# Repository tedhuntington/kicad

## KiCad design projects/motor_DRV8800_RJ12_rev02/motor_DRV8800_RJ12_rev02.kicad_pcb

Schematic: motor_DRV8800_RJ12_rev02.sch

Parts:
C1, C3, C4: .1uF (50v)
H1, H2: HOLE
J1, J2: TERMINAL_2X1
R1, R2: 3.3k
R3, R4, R5: 1k
R6: 10m
U1: DRV8800_RTY
U2: RJ12

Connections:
CS: R6.1, U1.7 (SENSE), U2.2
GND: C4.2, J1.2, R6.2, U1.2 (GND), U1.12 (GND), U1.17 (PAD), U2.1
MODE: R3.2, U1.16 (MODE)
Motor1OutA: J2.1, U1.6 (OUT+)
Motor1OutB: J2.2, U1.9 (OUT-)
unnamed: C1.1, U1.11 (CP2)
unnamed: C1.2, U1.10 (CP1)
unnamed: C3.2, U1.13 (VCP)
unnamed: R2.2, U1.15 (nFAULT)
unnamed: R1.2, U1.3 (nSLEEP)
unnamed: R5.2, U2.5
unnamed: R4.1, U2.3
unnamed: R3.1, U2.4
PHASE: R5.1, U1.1 (PHASE)
PWM: R4.2, U1.4 (ENABLE)
VDD: R1.1, R2.1, U2.6
Vin: C3.1, C4.1, J1.1, U1.8 (VBB)

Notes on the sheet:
8 to 36v
Out to Motor
Motor power source
VDD=3.3V
(0.5w)
note: above resistors protect MCU against short from motor driver failure

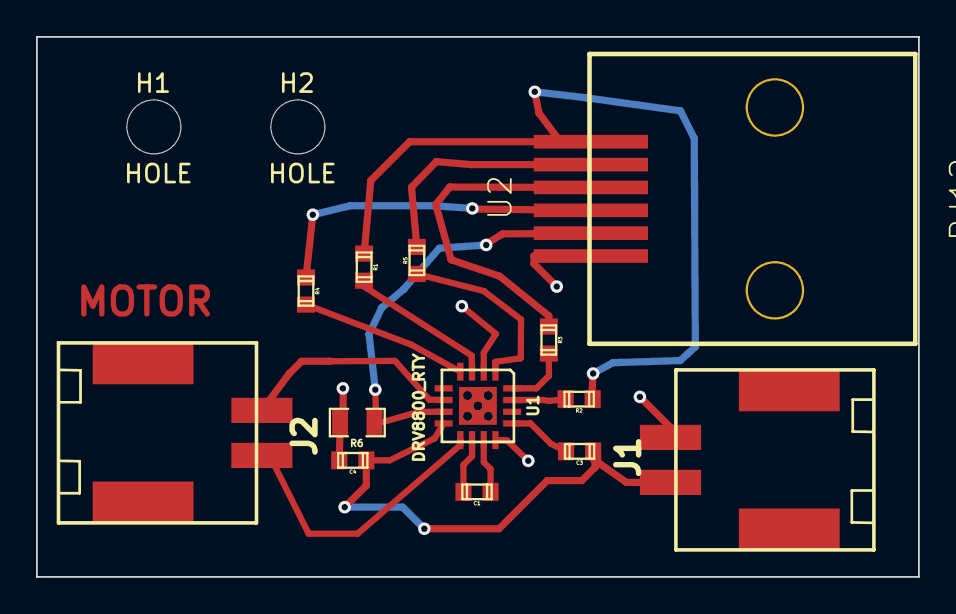
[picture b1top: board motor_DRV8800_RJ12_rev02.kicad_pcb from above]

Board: 2 copper layers, 49.0 x 30.0 mm, 15 parts (0 on the bottom side), 17 nets.

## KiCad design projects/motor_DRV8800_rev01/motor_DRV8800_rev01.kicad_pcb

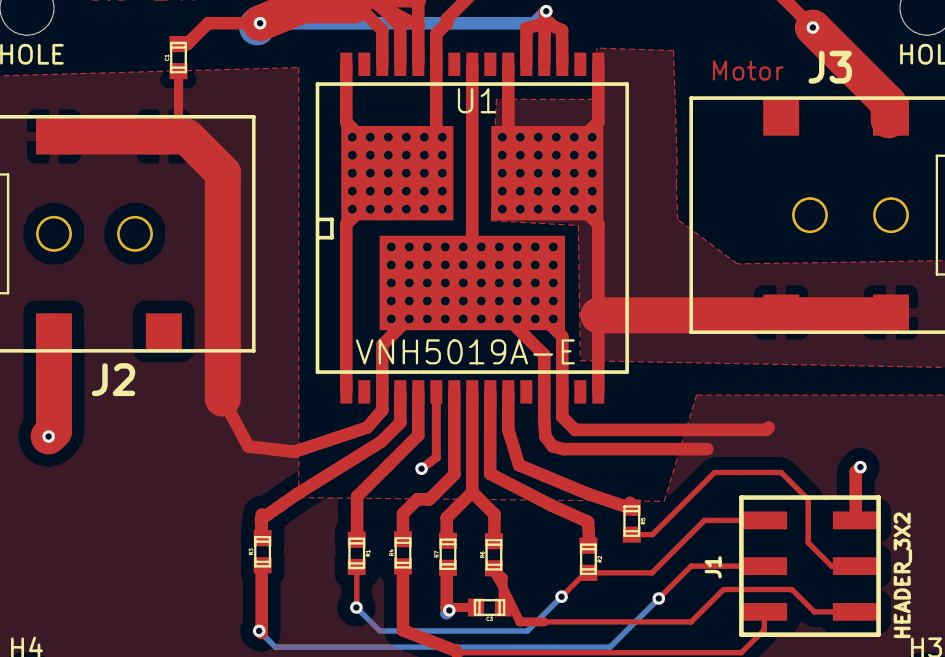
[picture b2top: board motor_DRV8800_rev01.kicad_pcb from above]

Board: 2 copper layers, 17 parts (0 on the bottom side), 15 nets.

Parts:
C1: .1uF (50v); TED_SM0603
C3: 33nF; TED_SM0603
H1, H2, H3, H4: HOLE; TED_Hole_3mm
J1: HEADER_3X2; TED_HEADER_3x2_SMT
J2, J3: DC_2.1MM; TED_DC_2.1mm_SMT
R1, R2: 3.3k; TED_SM0603
R3, R4, R5: 1k; TED_SM0603
R6: 10k; TED_SM0603
R7: 1.5k; TED_SM0603
U1: VNH5019A-E; TED_MultiPowerSO-30

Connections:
+2.8v: J1.1, R1.2, R2.2
CS: R6.2, R7.2, U1.8
GND: C1.2, C3.2, J1.6, J2.2, R7.1, U1.6, U1.18, U1.19, U1.20, U1.26, U1.27, U1.28
IN_A: R3.2, U1.4
IN_B: R5.1, U1.10
Motor1OutA: J3.2, U1.1, U1.25, U1.30, U1.33
Motor1OutB: J3.1, U1.15, U1.16, U1.21, U1.32
unnamed: J1.3, R4.1
unnamed: R2.1, U1.9
unnamed: R1.1, U1.5
unnamed: J1.2, R3.1
unnamed: J1.5, R5.2
unnamed: C3.1, J1.4, R6.1
PWM: R4.2, U1.7
Vin: C1.1, J2.1, U1.3, U1.12, U1.13, U1.23, U1.31

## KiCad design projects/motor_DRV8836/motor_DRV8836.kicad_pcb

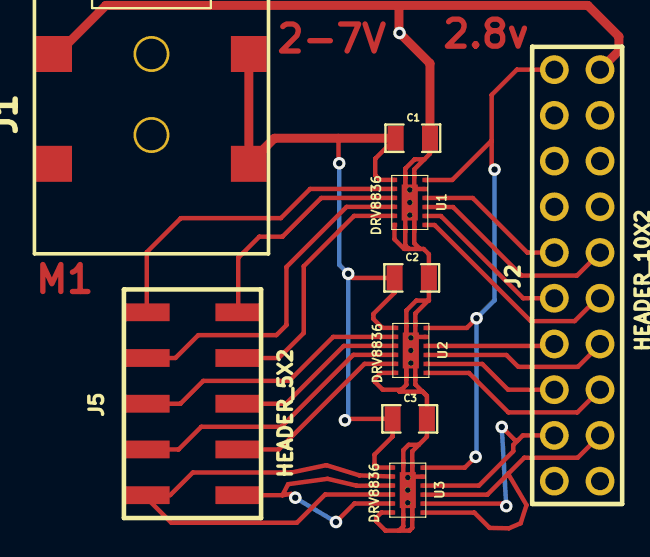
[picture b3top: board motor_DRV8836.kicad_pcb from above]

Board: 2 copper layers, 9 parts (0 on the bottom side), 23 nets.

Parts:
C1, C2, C3: 10uF; TED_SM0805
J1: Motor DC_2.1MM; TED_DC_2.1mm_SMT
J2: HEADER_10X2; TED_HEADER_10x2_BOTTOM_SIDE
J5: HEADER_5X2; TED_HEADER_5x2_SMT
U1, U2, U3: DRV8836; TED_WSON-12

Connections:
+2.8v: J2.1, U1.12, U2.12, U3.12
GND: C1.2, C2.2, C3.2, J1.2, J2.20, U1.6, U1.11, U1.PP, U2.6, U2.11, U2.PP, U3.6, U3.11, U3.PP
ICSPCLK_M1-: J2.16, U1.9
ICSPDAT_M1+: J2.5, U1.10
M2+: J2.6, U1.8
M2-: J2.15, U1.7
M3+: J2.7, U2.10
M3-: J2.14, U2.9
M4+: J2.8, U2.8
M4-: J2.13, U2.7
M5+: J2.9, U3.8, U3.10
M5-: J2.12, U3.7, U3.9
Motor1+: J5.1, U1.2
Motor1-: J5.10, U1.3
Motor2+: J5.2, U1.4
Motor2-: J5.9, U1.5
Motor3+: J5.3, U2.2
Motor3-: J5.8, U2.3
Motor4+: J5.4, U2.4
Motor4-: J5.7, U2.5
Motor5+: J5.5, U3.2, U3.4
Motor5-: J5.6, U3.3, U3.5
Vin: C1.1, C2.1, C3.1, J1.1, U1.1, U2.1, U3.1

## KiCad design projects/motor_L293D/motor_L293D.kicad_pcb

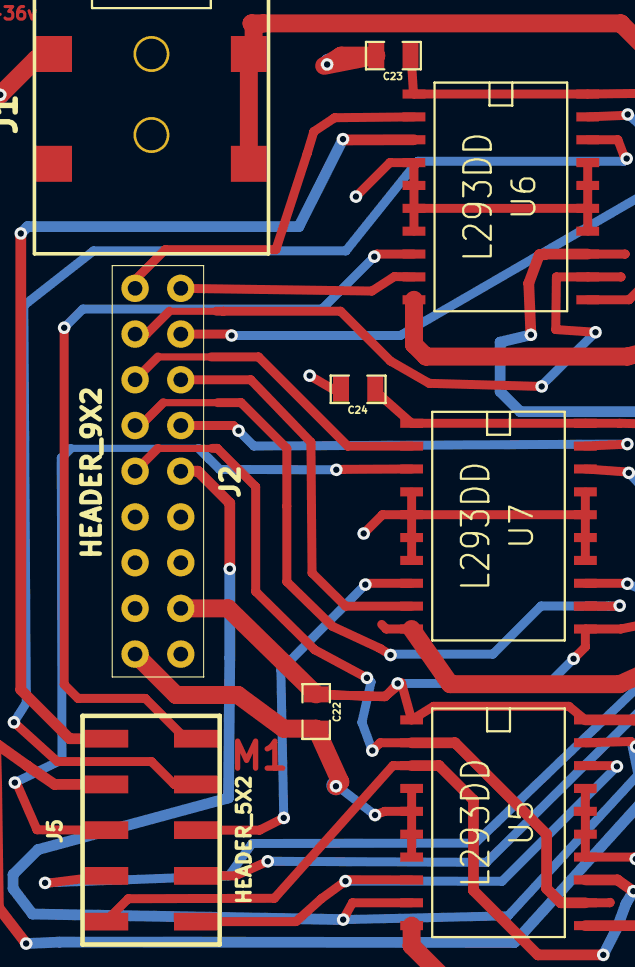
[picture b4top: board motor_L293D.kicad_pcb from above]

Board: 2 copper layers, 9 parts (0 on the bottom side), 23 nets.

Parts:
C22, C23, C24: .1uF; TED_SM0805
J1: Motor DC_2.1MM; TED_DC_2.1mm_SMT
J2: HEADER_9X2; TED_HEADER_9x2_TOP
J5: HEADER_5X2; TED_HEADER_5x2_SMT
U5, U6, U7: L293DD; SO20

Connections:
+5v_Vbus: C22.1, C23.1, C24.1, J2.11, U5.1, U5.11, U5.20, U6.1, U6.11, U6.20, U7.1, U7.11, U7.20
GND: C22.2, C23.2, C24.2, J1.2, J2.9, U5.4, U5.5, U5.6, U5.7, U5.14, U5.15, U5.16, U5.17, U6.4, U6.5, U6.6, U6.7, U6.14, U6.15, U6.16, U6.17, U7.4, U7.5, U7.6, U7.7, U7.14, U7.15, U7.16, U7.17
ICSPCLK_M1-: J2.18, U6.9
ICSPDAT_M1+: J2.1, U6.2
M2+: J2.2, U6.12
M2-: J2.17, U6.19
M3+: J2.3, U7.2
M3-: J2.16, U7.9
M4+: J2.4, U7.12
M4-: J2.15, U7.19
M5+: J2.5, U5.2, U5.12
M5-: J2.14, U5.9, U5.19
Motor1+: J5.1, U6.3
Motor1-: J5.10, U6.8
Motor2+: J5.2, U6.13
Motor2-: J5.9, U6.18
Motor3+: J5.3, U7.3
Motor3-: J5.8, U7.8
Motor4+: J5.4, U7.13
Motor4-: J5.7, U7.18
Motor5+: J5.5, U5.3, U5.13
Motor5-: J5.6, U5.8, U5.18
Vin: J1.1, U5.10, U6.10, U7.10

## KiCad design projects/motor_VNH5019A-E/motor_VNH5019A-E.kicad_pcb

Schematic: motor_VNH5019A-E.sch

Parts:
C1: 470uF (25v)
C2: .1uF (25v)
C3: 33nF
J1: DC_2.1MM; TED_DC_2.1mm
J2: HEADER_9X2
J3, J4: TRM_3.5MM_2P; TED_TERMINAL_3.5MM_2PIN
R1: 1.5k
R2: 10k
R3, R9: 3.3k
R4, R5, R6, R7, R8: 1k
U1: VNH5019A-E

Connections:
+3.3v: J2.10, R3.2, R9.2
CS: R1.2, R2.2, U1.8 (CS)
CS_DIS: J2.4, U1.6 (CS_DIS)
ENA_DIAGA: R7.1, R9.1, U1.5 (ENA/DIAGA)
ENB_DIAGB: R3.1, R8.1, U1.9 (ENB/DIAGB)
GND: C1.2, C2.2, C3.2, J1.2, J2.9, J3.2, R1.1, U1.18 (GNDB), U1.19 (GNDB), U1.20 (GNDB), U1.26 (GNDA), U1.27 (GNDA), U1.28 (GNDA)
ICSPCLK_M1-: R6.1, U1.10 (INB)
ICSPDAT_M1+: R4.2, U1.4 (INA)
Motor1OutA: J4.2, U1.1 (OUTA), U1.25 (OUTA), U1.30 (OUTA), U1.33 (OUTA/HEATSLG2)
Motor1OutB: J4.1, U1.15 (OUTB), U1.16 (OUTB), U1.21 (OUTB), U1.32 (OUTB/HEATSLG3)
unnamed: C3.1, J2.3, R2.1
unnamed: J2.1, R4.1
unnamed: J2.18, R6.2
unnamed: J2.2, R5.1
unnamed: J2.17, R7.2
unnamed: J2.16, R8.2
PWM: R5.2, U1.7 (PWM)
Vin: C1.1, C2.1, J1.1, J3.1, U1.3 (VCC), U1.12 (VBAT), U1.13 (VCC), U1.23 (VCC), U1.31 (VCC/HEATSLG1)

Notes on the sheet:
+5.5 to +24v
Out to Motor
Power source (Battery)
Alternative battery source (AC adapter)
PORT B (FEMALE, THROUGH-HOLE)
todo: verify that the large capacitor can be replaced by a TVS

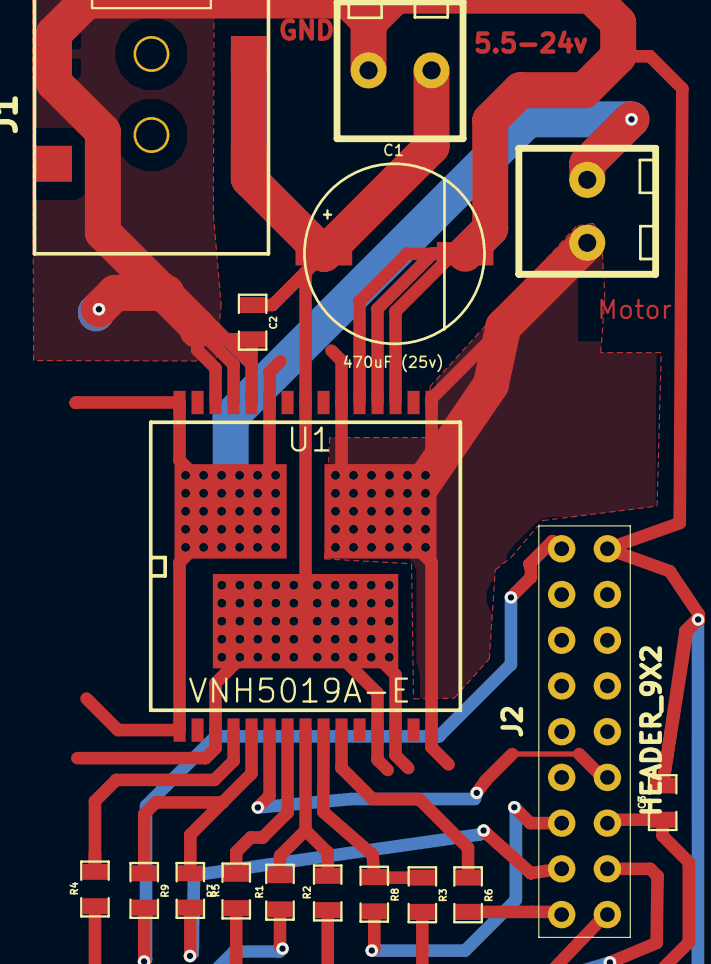
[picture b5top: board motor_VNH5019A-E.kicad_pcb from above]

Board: 2 copper layers, 17 parts (0 on the bottom side), 18 nets.
